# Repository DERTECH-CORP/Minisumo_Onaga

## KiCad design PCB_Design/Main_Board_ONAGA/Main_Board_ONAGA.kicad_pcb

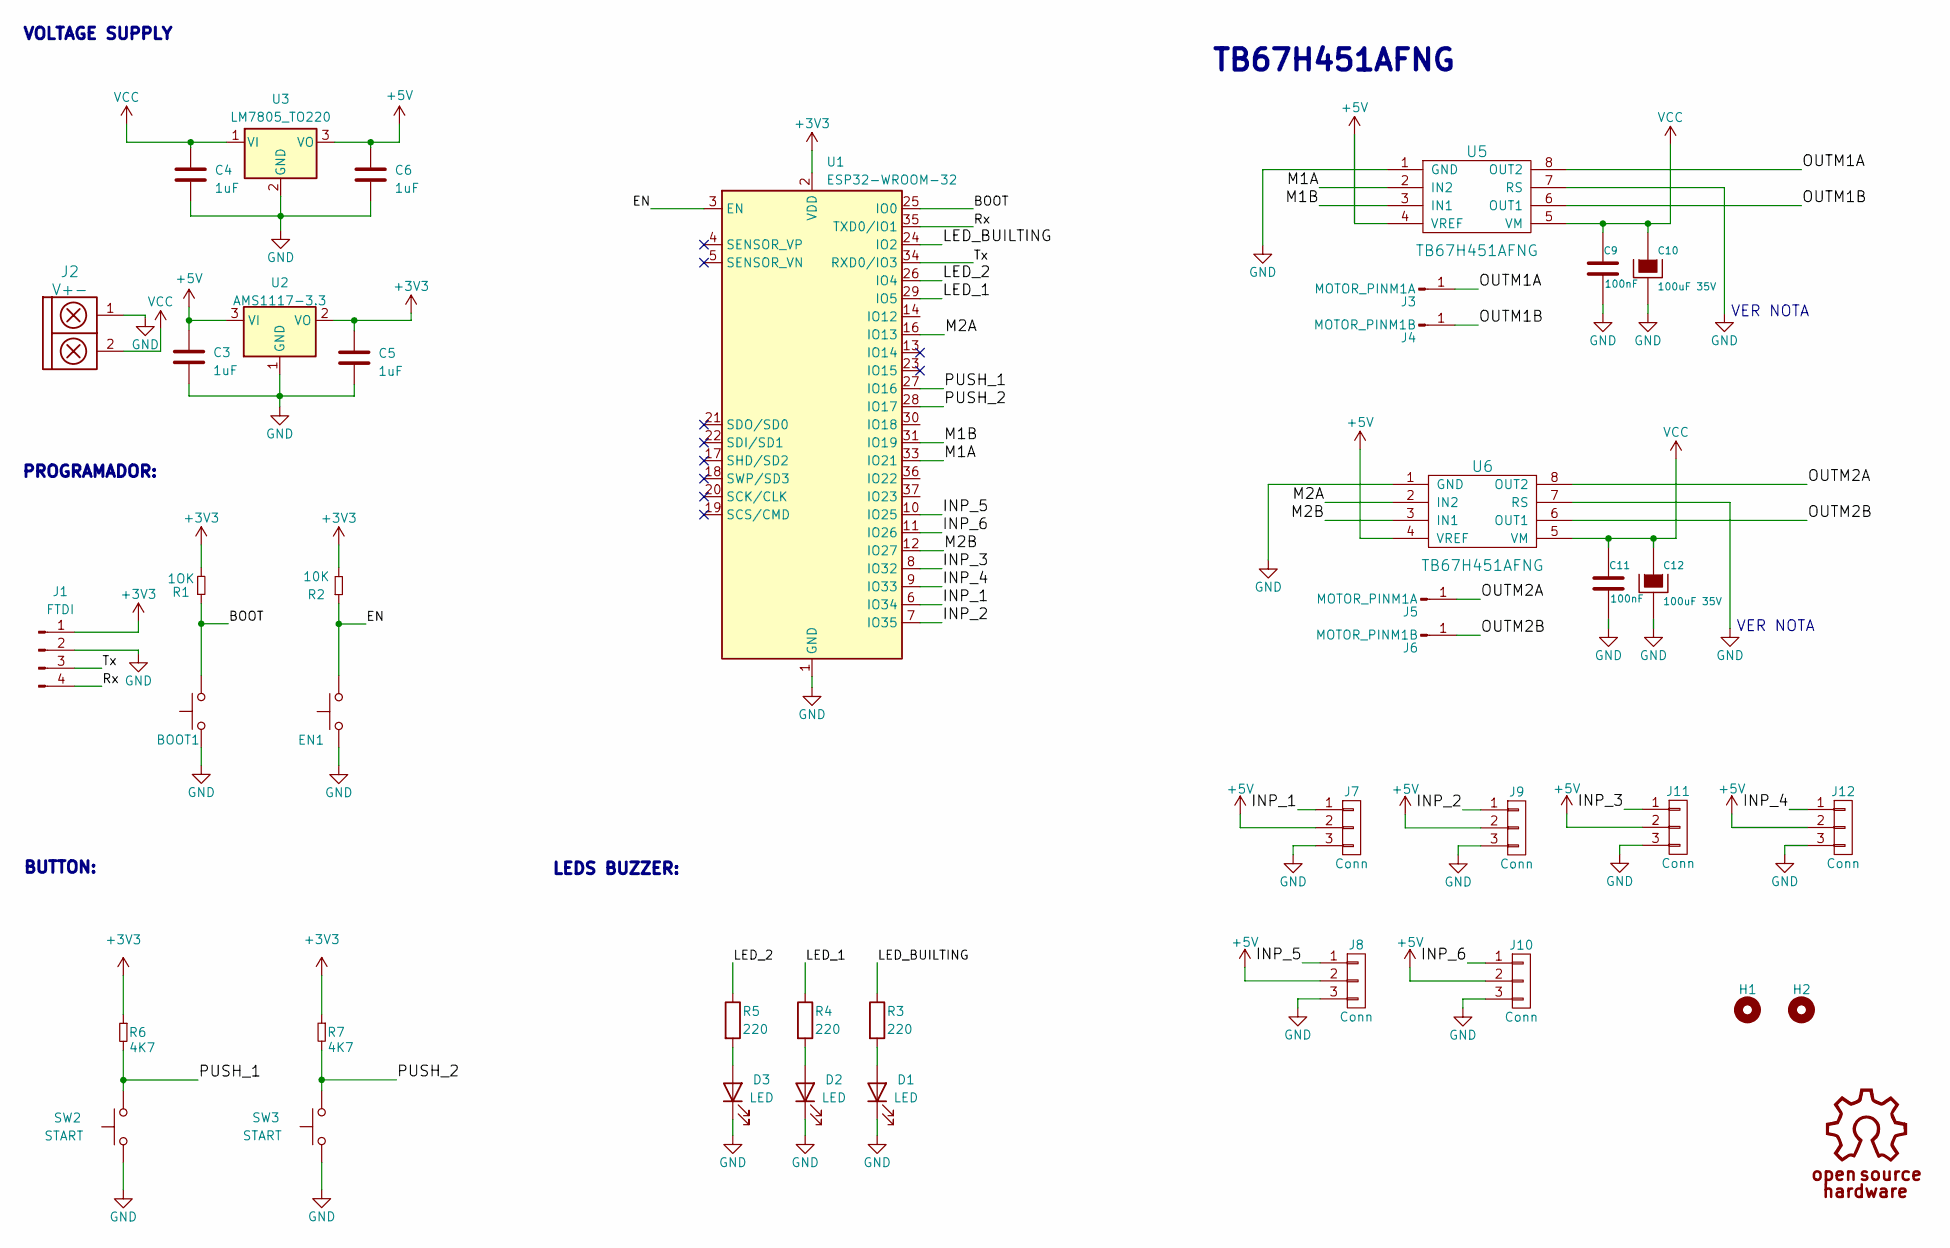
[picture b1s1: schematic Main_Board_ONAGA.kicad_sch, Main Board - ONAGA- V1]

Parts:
BOOT1: SW_Push; SW_SPST_B3U-1000P
C3, C4, C5, C6: 1uF; C_0805_2012Metric_Pad1.18x1.45mm_HandSolder
C9, C11: 100nF; C_0805
C10, C12: 100uF 35V; CP_Radial_D5.0mm_P2.50mm
D1, D2, D3: LED; Led_0805
EN1: SW_Push; SW_SPST_B3U-1000P
H1, H2: Mounting_Hole; Separador_M3_5mm
J1: FTDI; PinHeader_1x04_P2.54mm_Horizontal
J2: V+-; BORNERA2_AZUL
J3, J5: MOTOR_PINM1A; pad_3mm
J4, J6: MOTOR_PINM1B; pad_3mm
J7, J8, J9, J10, J11, J12: Conn; PinHeader_1x03_P2.54mm_Vertical
R1: 1OK; R_1206
R2: 10K; R_1206
R3, R4, R5: 220; R_1206
R6, R7: 4K7; R_1206
SW2, SW3: START; SW_PUSH_6mm_H5mm
U1: ESP32-WROOM-32; ESP32-WROOM-32D
U2: AMS1117-3.3; SOT-223-3_TabPin2
U3: LM7805_TO220; TO-220-3_Vertical
U5, U6: TB67H451AFNG; SSOP-8_disipa

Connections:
+3V3: C5.1, J1.1, R1.2, R2.2, R6.1, R7.1, U1.2 (VDD), U2.2 (VO)
+5V: C3.1, C6.1, J7.2, J8.2, J9.2, J10.2, J11.2, J12.2, U2.3 (VI), U3.3 (VO), U5.4 (VREF), U6.4 (VREF)
/BOOT: BOOT1.2, R1.1, U1.25 (IO0)
/EN: EN1.2, R2.1, U1.3 (EN)
/INP_1: J7.1, U1.6 (IO34)
/INP_2: J9.1, U1.7 (IO35)
/INP_3: J11.1, U1.8 (IO32)
/INP_4: J12.1, U1.9 (IO33)
/INP_5: J8.1, U1.10 (IO25)
/INP_6: J10.1, U1.11 (IO26)
/LED_1: R4.1, U1.29 (IO5)
/LED_2: R5.1, U1.26 (IO4)
/LED_BUILTING: R3.1, U1.24 (IO2)
/M1A: U1.33 (IO21), U5.2 (IN2)
/M1B: U1.31 (IO19), U5.3 (IN1)
/M2A: U1.16 (IO13), U6.2 (IN2)
/M2B: U1.12 (IO27), U6.3 (IN1)
/OUTM1A: J3.1, U5.8 (OUT2)
/OUTM1B: J4.1, U5.6 (OUT1)
/OUTM2A: J5.1, U6.8 (OUT2)
/OUTM2B: J6.1, U6.6 (OUT1)
/PUSH_1: R6.2, SW2.2, U1.27 (IO16)
/PUSH_2: R7.2, SW3.2, U1.28 (IO17)
/Rx: J1.4, U1.35 (TXD0/IO1)
/Tx: J1.3, U1.34 (RXD0/IO3)
GND: BOOT1.1, C3.2, C4.2, C5.2, C6.2, C9.2, C10.2, C11.2, C12.2, D1.1 (K), D2.1 (K), D3.1 (K), EN1.1, J1.2, J2.1, J7.3, J8.3, J9.3, J10.3, J11.3, J12.3, SW2.1, SW3.1, U1.1 (GND), U1.15 (GND), U1.38 (GND), U1.39 (GND), U2.1 (GND), U3.2 (GND), U5.1 (GND), U5.7 (RS), U6.1 (GND), U6.7 (RS)
unnamed: D1.2 (A), R3.2
unnamed: D2.2 (A), R4.2
unnamed: D3.2 (A), R5.2
VCC: C4.1, C9.1, C10.1, C11.1, C12.1, J2.2, U3.1 (VI), U5.5 (VM), U6.5 (VM)

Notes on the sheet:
LEDS BUZZER:
BUTTON:
VER NOTA
VOLTAGE SUPPLY
TB67H451AFNG
PROGRAMADOR:

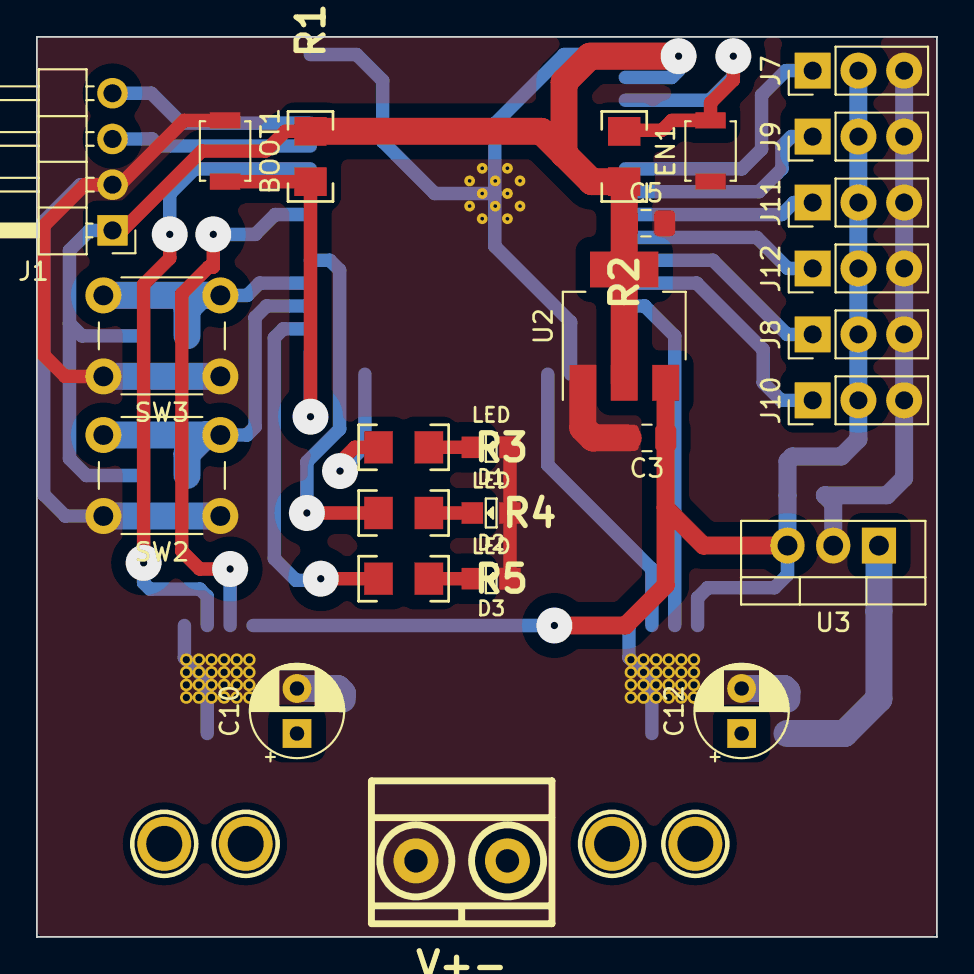
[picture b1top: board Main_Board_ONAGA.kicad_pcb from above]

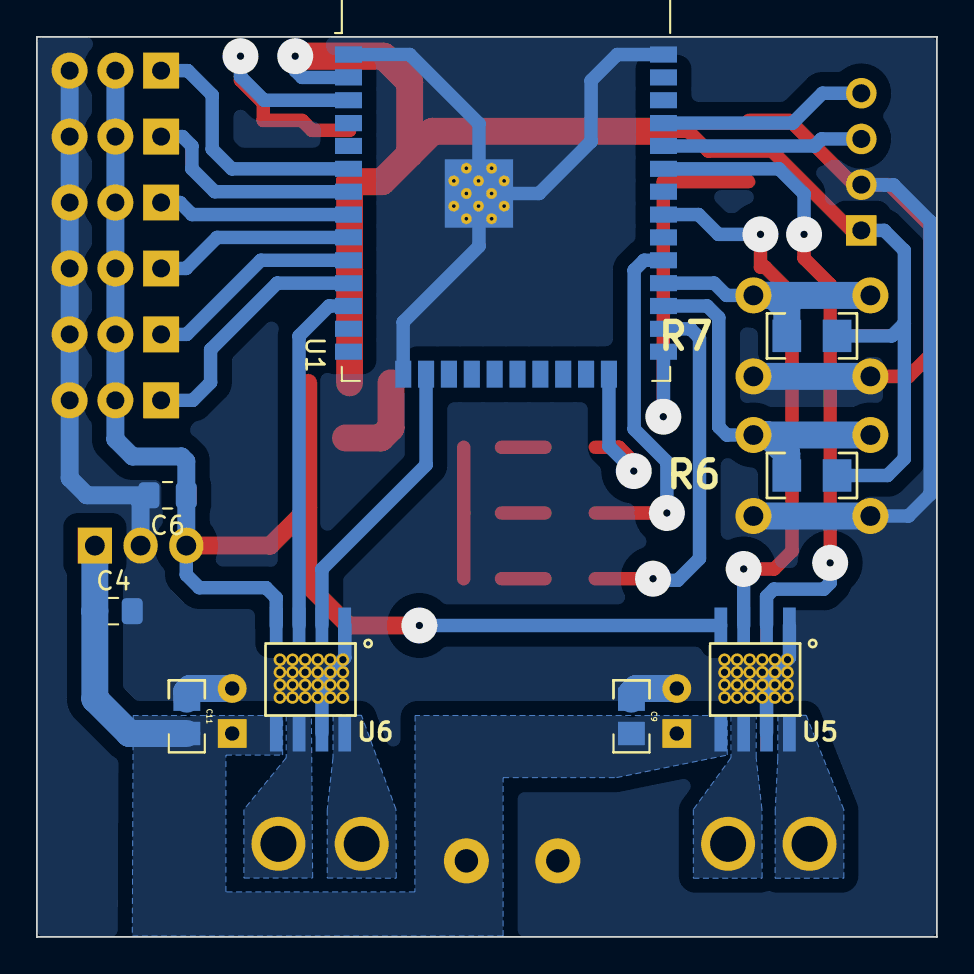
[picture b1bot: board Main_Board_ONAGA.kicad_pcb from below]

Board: 2 copper layers, 50.0 x 50.0 mm, 39 parts (9 on the bottom side), 30 nets.

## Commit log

2023-10-03 Creacion del SCH y PCB de la MainBoard
2023-10-04 Diseño de PCB en proceso
2023-10-05 Chequeo de PCB
2023-10-05 3D prototipo terminado
2023-10-06 Edicion 3D
2023-10-06 braquet motor terminado
